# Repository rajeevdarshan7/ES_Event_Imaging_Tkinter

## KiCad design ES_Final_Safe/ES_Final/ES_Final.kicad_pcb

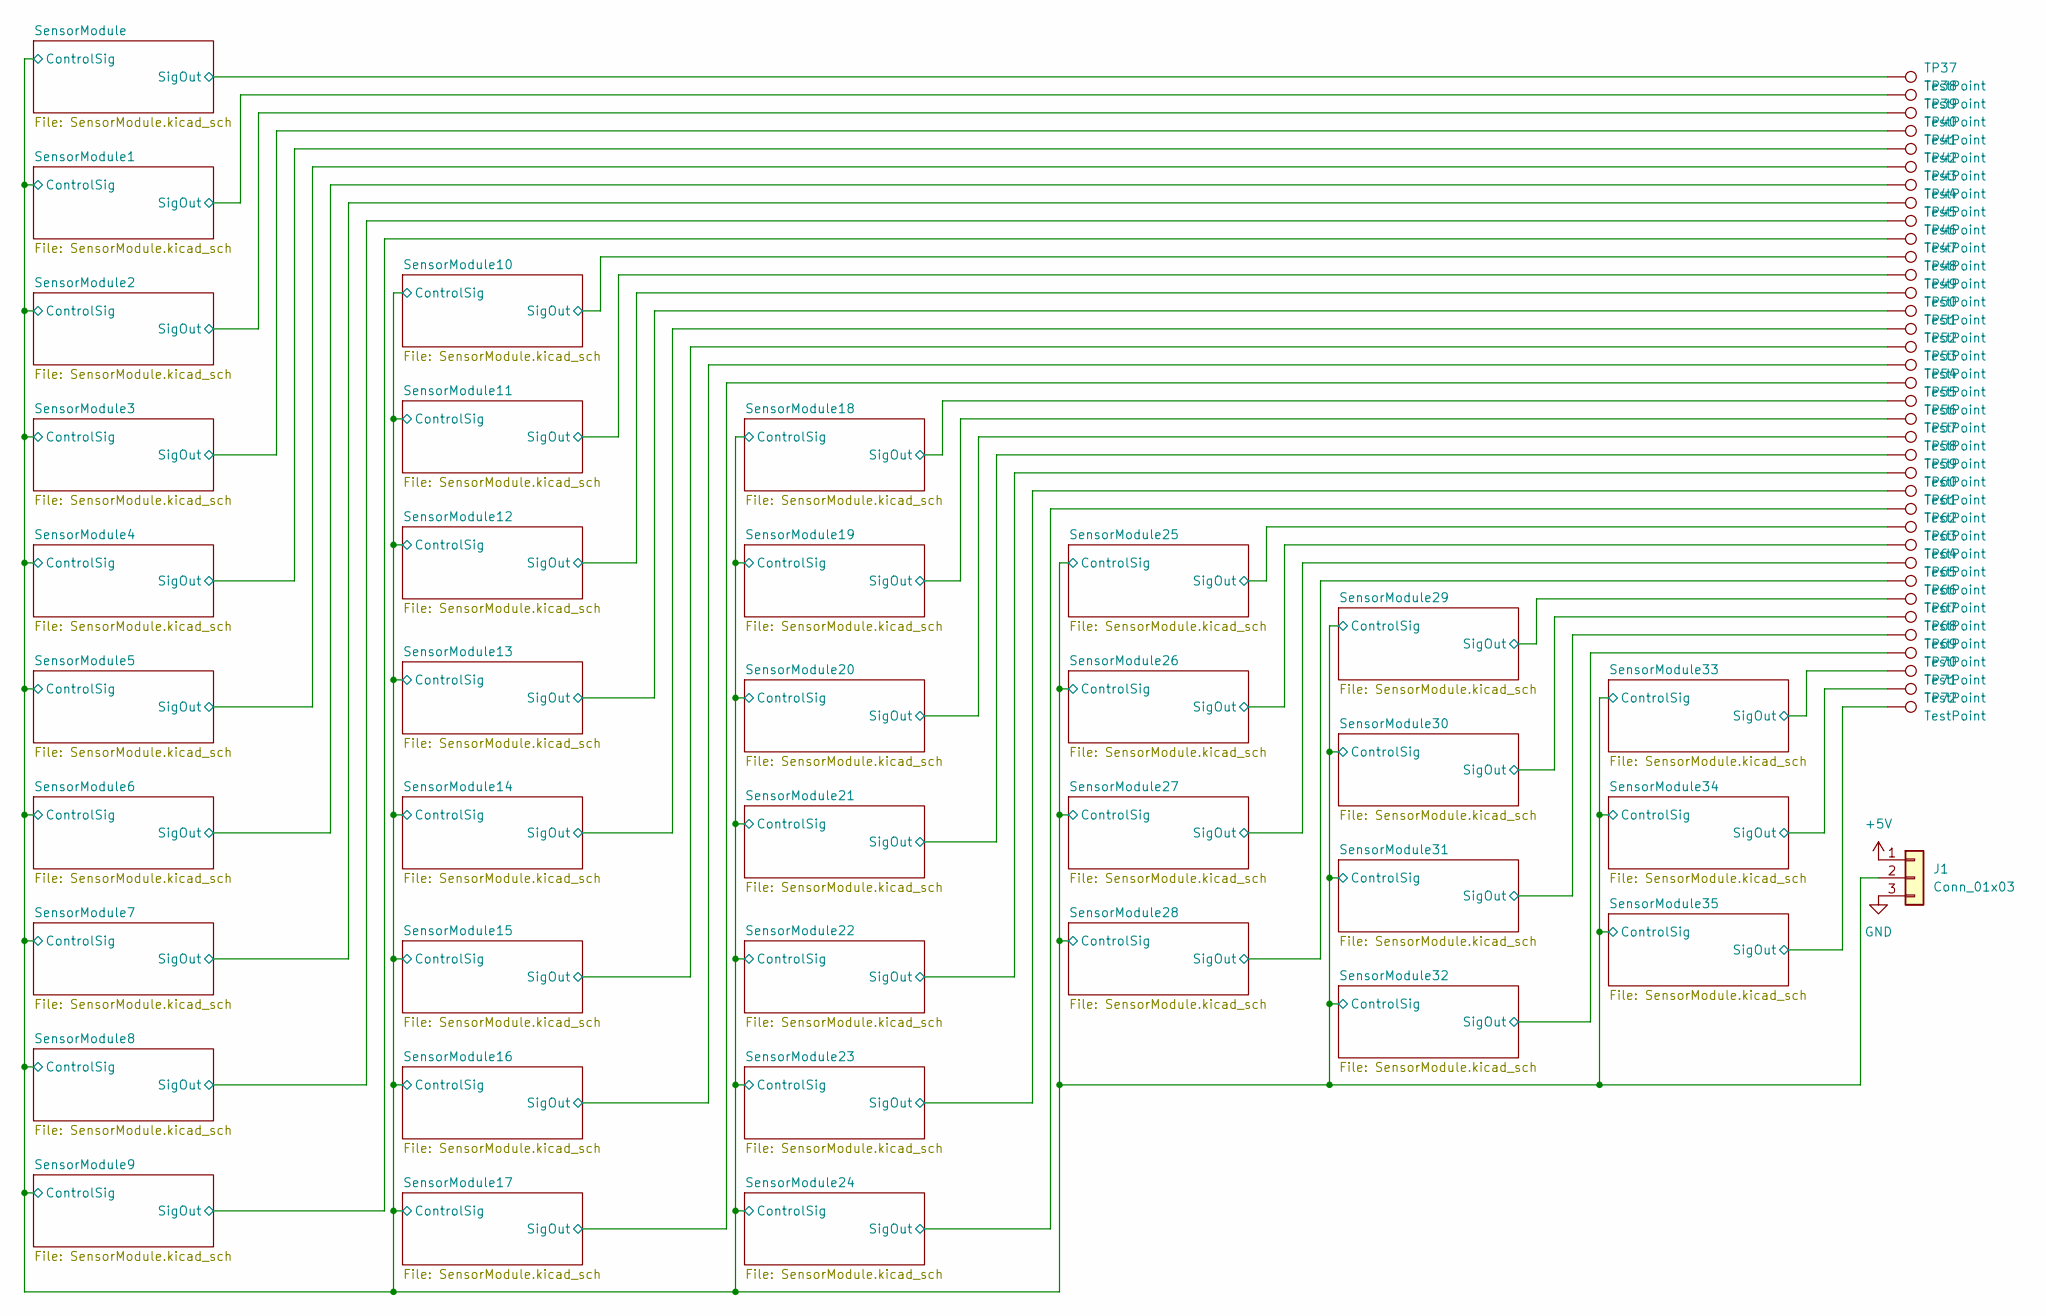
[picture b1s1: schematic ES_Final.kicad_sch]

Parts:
J1: Conn_01x03; JST_XH_B3B-XH-A_1x03_P2.50mm_Vertical
TP37, TP38, TP39, TP40, TP41, TP42, TP43, TP44, TP45, TP46, TP47, TP48, TP49, TP50, TP51, TP52, TP53, TP54, TP55, TP56, TP57, TP58, TP59, TP60, TP61, TP62, TP63, TP64, TP65, TP66, TP67, TP68, TP69, TP70, TP71, TP72: TestPoint; TestPoint_Pad_D1.0mm

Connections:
+5V: J1.1; also elsewhere on the board
/SensorModule1/SigOut: TP38.1; also elsewhere on the board
/SensorModule2/SigOut: TP39.1; also elsewhere on the board
/SensorModule3/SigOut: TP40.1; also elsewhere on the board
/SensorModule4/SigOut: TP41.1; also elsewhere on the board
/SensorModule5/SigOut: TP42.1; also elsewhere on the board
/SensorModule6/SigOut: TP43.1; also elsewhere on the board
/SensorModule7/SigOut: TP44.1; also elsewhere on the board
/SensorModule8/SigOut: TP45.1; also elsewhere on the board
/SensorModule9/SigOut: TP46.1; also elsewhere on the board
/SensorModule10/SigOut: TP47.1; also elsewhere on the board
/SensorModule11/SigOut: TP48.1; also elsewhere on the board
/SensorModule12/SigOut: TP49.1; also elsewhere on the board
/SensorModule13/SigOut: TP50.1; also elsewhere on the board
/SensorModule14/SigOut: TP51.1; also elsewhere on the board
/SensorModule15/SigOut: TP52.1; also elsewhere on the board
/SensorModule16/SigOut: TP53.1; also elsewhere on the board
/SensorModule17/SigOut: TP54.1; also elsewhere on the board
/SensorModule18/SigOut: TP55.1; also elsewhere on the board
/SensorModule19/SigOut: TP56.1; also elsewhere on the board
/SensorModule20/SigOut: TP57.1; also elsewhere on the board
/SensorModule21/SigOut: TP58.1; also elsewhere on the board
/SensorModule22/SigOut: TP59.1; also elsewhere on the board
/SensorModule23/SigOut: TP60.1; also elsewhere on the board
/SensorModule24/SigOut: TP61.1; also elsewhere on the board
/SensorModule25/SigOut: TP62.1; also elsewhere on the board
/SensorModule26/SigOut: TP63.1; also elsewhere on the board
/SensorModule27/SigOut: TP64.1; also elsewhere on the board
/SensorModule28/SigOut: TP65.1; also elsewhere on the board
/SensorModule29/SigOut: TP66.1; also elsewhere on the board
/SensorModule30/SigOut: TP67.1; also elsewhere on the board
/SensorModule31/SigOut: TP68.1; also elsewhere on the board
/SensorModule32/SigOut: TP69.1; also elsewhere on the board
/SensorModule33/SigOut: TP70.1; also elsewhere on the board
/SensorModule34/SigOut: TP71.1; also elsewhere on the board
/SensorModule35/SigOut: TP72.1; also elsewhere on the board
/SensorModule/ControlSig: J1.2; also elsewhere on the board
/SensorModule/SigOut: TP37.1; also elsewhere on the board
GND: J1.3; also elsewhere on the board

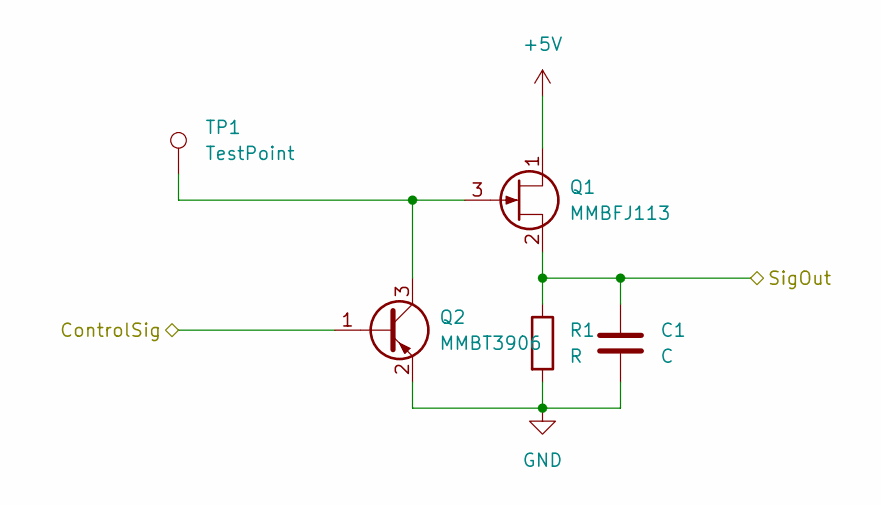
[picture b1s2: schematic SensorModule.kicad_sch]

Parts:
C1: C; C_0805_2012Metric_Pad1.18x1.45mm_HandSolder
Q1: MMBFJ113; SOT-23
Q2: MMBT3906; SOT-23
R1: R; R_0805_2012Metric_Pad1.20x1.40mm_HandSolder
TP1: TestPoint; TestPoint_Pad_1.0x1.0mm

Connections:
+5V: Q1.1 (D); also elsewhere on the board
/SensorModule/ControlSig: Q2.1 (B); also elsewhere on the board
/SensorModule/SigOut: C1.1, Q1.2 (S), R1.1; also elsewhere on the board
GND: C1.2, Q2.2 (E), R1.2; also elsewhere on the board
unnamed: Q1.3 (G), Q2.3 (C), TP1.1

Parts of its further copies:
C2, C3, C4, C5, C6, C7, C8, C9, C10, C11, C12, C13, C14, C15, C16, C17, C18, C19, C20, C21, C22, C23, C24, C25, C26, C27, C28, C29, C30, C31, C32, C33, C34, C35, C36: C; C_0805_2012Metric_Pad1.18x1.45mm_HandSolder
Q3, Q5, Q7, Q9, Q11, Q13, Q15, Q17, Q19, Q21, Q23, Q25, Q27, Q29, Q31, Q33, Q35, Q37, Q39, Q41, Q43, Q45, Q47, Q49, Q51, Q53, Q55, Q57, Q59, Q61, Q63, Q65, Q67, Q69, Q71: MMBT3906; SOT-23
Q4, Q6, Q8, Q10, Q12, Q14, Q16, Q18, Q20, Q22, Q24, Q26, Q28, Q30, Q32, Q34, Q36, Q38, Q40, Q42, Q44, Q46, Q48, Q50, Q52, Q54, Q56, Q58, Q60, Q62, Q64, Q66, Q68, Q70, Q72: MMBFJ113; SOT-23
R2, R3, R4, R5, R6, R7, R8, R9, R10, R11, R12, R13, R14, R15, R16, R17, R18, R19, R20, R21, R22, R23, R24, R25, R26, R27, R28, R29, R30, R31, R32, R33, R34, R35, R36: R; R_0805_2012Metric_Pad1.20x1.40mm_HandSolder
TP2, TP3, TP4, TP5, TP6, TP7, TP8, TP9, TP10, TP11, TP12, TP13, TP14, TP15, TP16, TP17, TP18, TP19, TP20, TP21, TP22, TP23, TP24, TP25, TP26, TP27, TP28, TP29, TP30, TP31, TP32, TP33, TP34, TP35, TP36: TestPoint; TestPoint_Pad_1.0x1.0mm

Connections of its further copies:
+5V: Q4.1 (D), Q6.1 (D), Q8.1 (D), Q10.1 (D), Q12.1 (D), Q14.1 (D), Q16.1 (D), Q18.1 (D), Q20.1 (D), Q22.1 (D), Q24.1 (D), Q26.1 (D), Q28.1 (D), Q30.1 (D), Q32.1 (D), Q34.1 (D), Q36.1 (D), Q38.1 (D), Q40.1 (D), Q42.1 (D), Q44.1 (D), Q46.1 (D), Q48.1 (D), Q50.1 (D), Q52.1 (D), Q54.1 (D), Q56.1 (D), Q58.1 (D), Q60.1 (D), Q62.1 (D), Q64.1 (D), Q66.1 (D), Q68.1 (D), Q70.1 (D), Q72.1 (D); also elsewhere on the board
/SensorModule1/SigOut: C2.1, Q4.2 (S), R2.1; also elsewhere on the board
/SensorModule2/SigOut: C3.1, Q6.2 (S), R3.1; also elsewhere on the board
/SensorModule3/SigOut: C4.1, Q8.2 (S), R4.1; also elsewhere on the board
/SensorModule4/SigOut: C5.1, Q10.2 (S), R5.1; also elsewhere on the board
/SensorModule5/SigOut: C6.1, Q12.2 (S), R6.1; also elsewhere on the board
/SensorModule6/SigOut: C7.1, Q14.2 (S), R7.1; also elsewhere on the board
/SensorModule7/SigOut: C8.1, Q16.2 (S), R8.1; also elsewhere on the board
/SensorModule8/SigOut: C9.1, Q18.2 (S), R9.1; also elsewhere on the board
/SensorModule9/SigOut: C10.1, Q20.2 (S), R10.1; also elsewhere on the board
/SensorModule10/SigOut: C11.1, Q22.2 (S), R11.1; also elsewhere on the board
/SensorModule11/SigOut: C12.1, Q24.2 (S), R12.1; also elsewhere on the board
/SensorModule12/SigOut: C13.1, Q26.2 (S), R13.1; also elsewhere on the board
/SensorModule13/SigOut: C14.1, Q28.2 (S), R14.1; also elsewhere on the board
/SensorModule14/SigOut: C15.1, Q30.2 (S), R15.1; also elsewhere on the board
/SensorModule15/SigOut: C16.1, Q32.2 (S), R16.1; also elsewhere on the board
/SensorModule16/SigOut: C17.1, Q34.2 (S), R17.1; also elsewhere on the board
/SensorModule17/SigOut: C18.1, Q36.2 (S), R18.1; also elsewhere on the board
/SensorModule18/SigOut: C19.1, Q38.2 (S), R19.1; also elsewhere on the board
/SensorModule19/SigOut: C20.1, Q40.2 (S), R20.1; also elsewhere on the board
/SensorModule20/SigOut: C21.1, Q42.2 (S), R21.1; also elsewhere on the board
/SensorModule21/SigOut: C22.1, Q44.2 (S), R22.1; also elsewhere on the board
/SensorModule22/SigOut: C23.1, Q46.2 (S), R23.1; also elsewhere on the board
/SensorModule23/SigOut: C24.1, Q48.2 (S), R24.1; also elsewhere on the board
/SensorModule24/SigOut: C25.1, Q50.2 (S), R25.1; also elsewhere on the board
/SensorModule25/SigOut: C26.1, Q52.2 (S), R26.1; also elsewhere on the board
/SensorModule26/SigOut: C27.1, Q54.2 (S), R27.1; also elsewhere on the board
/SensorModule27/SigOut: C28.1, Q56.2 (S), R28.1; also elsewhere on the board
/SensorModule28/SigOut: C29.1, Q58.2 (S), R29.1; also elsewhere on the board
/SensorModule29/SigOut: C30.1, Q60.2 (S), R30.1; also elsewhere on the board
/SensorModule30/SigOut: C31.1, Q62.2 (S), R31.1; also elsewhere on the board
/SensorModule31/SigOut: C32.1, Q64.2 (S), R32.1; also elsewhere on the board
/SensorModule32/SigOut: C33.1, Q66.2 (S), R33.1; also elsewhere on the board
/SensorModule33/SigOut: C34.1, Q68.2 (S), R34.1; also elsewhere on the board
/SensorModule34/SigOut: C35.1, Q70.2 (S), R35.1; also elsewhere on the board
/SensorModule35/SigOut: C36.1, Q72.2 (S), R36.1; also elsewhere on the board
/SensorModule/ControlSig: Q3.1 (B), Q5.1 (B), Q7.1 (B), Q9.1 (B), Q11.1 (B), Q13.1 (B), Q15.1 (B), Q17.1 (B), Q19.1 (B), Q21.1 (B), Q23.1 (B), Q25.1 (B), Q27.1 (B), Q29.1 (B), Q31.1 (B), Q33.1 (B), Q35.1 (B), Q37.1 (B), Q39.1 (B), Q41.1 (B), Q43.1 (B), Q45.1 (B), Q47.1 (B), Q49.1 (B), Q51.1 (B), Q53.1 (B), Q55.1 (B), Q57.1 (B), Q59.1 (B), Q61.1 (B), Q63.1 (B), Q65.1 (B), Q67.1 (B), Q69.1 (B), Q71.1 (B); also elsewhere on the board
GND: C2.2, C3.2, C4.2, C5.2, C6.2, C7.2, C8.2, C9.2, C10.2, C11.2, C12.2, C13.2, C14.2, C15.2, C16.2, C17.2, C18.2, C19.2, C20.2, C21.2, C22.2, C23.2, C24.2, C25.2, C26.2, C27.2, C28.2, C29.2, C30.2, C31.2, C32.2, C33.2, C34.2, C35.2, C36.2, Q3.2 (E), Q5.2 (E), Q7.2 (E), Q9.2 (E), Q11.2 (E), Q13.2 (E), Q15.2 (E), Q17.2 (E), Q19.2 (E), Q21.2 (E), Q23.2 (E), Q25.2 (E), Q27.2 (E), Q29.2 (E), Q31.2 (E), Q33.2 (E), Q35.2 (E), Q37.2 (E), Q39.2 (E), Q41.2 (E), Q43.2 (E), Q45.2 (E), Q47.2 (E), Q49.2 (E), Q51.2 (E), Q53.2 (E), Q55.2 (E), Q57.2 (E), Q59.2 (E), Q61.2 (E), Q63.2 (E), Q65.2 (E), Q67.2 (E), Q69.2 (E), Q71.2 (E), R2.2, R3.2, R4.2, R5.2, R6.2, R7.2, R8.2, R9.2, R10.2, R11.2, R12.2, R13.2, R14.2, R15.2, R16.2, R17.2, R18.2, R19.2, R20.2, R21.2, R22.2, R23.2, R24.2, R25.2, R26.2, R27.2, R28.2, R29.2, R30.2, R31.2, R32.2, R33.2, R34.2, R35.2, R36.2; also elsewhere on the board
unnamed: Q3.3 (C), Q4.3 (G), TP2.1
unnamed: Q5.3 (C), Q6.3 (G), TP3.1
unnamed: Q7.3 (C), Q8.3 (G), TP4.1
unnamed: Q9.3 (C), Q10.3 (G), TP5.1
unnamed: Q11.3 (C), Q12.3 (G), TP6.1
unnamed: Q13.3 (C), Q14.3 (G), TP7.1
unnamed: Q15.3 (C), Q16.3 (G), TP8.1
unnamed: Q17.3 (C), Q18.3 (G), TP9.1
unnamed: Q19.3 (C), Q20.3 (G), TP10.1
unnamed: Q21.3 (C), Q22.3 (G), TP11.1
unnamed: Q23.3 (C), Q24.3 (G), TP12.1
unnamed: Q25.3 (C), Q26.3 (G), TP13.1
unnamed: Q27.3 (C), Q28.3 (G), TP14.1
unnamed: Q29.3 (C), Q30.3 (G), TP15.1
unnamed: Q31.3 (C), Q32.3 (G), TP16.1
unnamed: Q33.3 (C), Q34.3 (G), TP17.1
unnamed: Q35.3 (C), Q36.3 (G), TP18.1
unnamed: Q37.3 (C), Q38.3 (G), TP19.1
unnamed: Q39.3 (C), Q40.3 (G), TP20.1
unnamed: Q41.3 (C), Q42.3 (G), TP21.1
unnamed: Q43.3 (C), Q44.3 (G), TP22.1
unnamed: Q45.3 (C), Q46.3 (G), TP23.1
unnamed: Q47.3 (C), Q48.3 (G), TP24.1
unnamed: Q49.3 (C), Q50.3 (G), TP25.1
unnamed: Q51.3 (C), Q52.3 (G), TP26.1
unnamed: Q53.3 (C), Q54.3 (G), TP27.1
unnamed: Q55.3 (C), Q56.3 (G), TP28.1
unnamed: Q57.3 (C), Q58.3 (G), TP29.1
unnamed: Q59.3 (C), Q60.3 (G), TP30.1
unnamed: Q61.3 (C), Q62.3 (G), TP31.1
unnamed: Q63.3 (C), Q64.3 (G), TP32.1
unnamed: Q65.3 (C), Q66.3 (G), TP33.1
unnamed: Q67.3 (C), Q68.3 (G), TP34.1
unnamed: Q69.3 (C), Q70.3 (G), TP35.1
unnamed: Q71.3 (C), Q72.3 (G), TP36.1

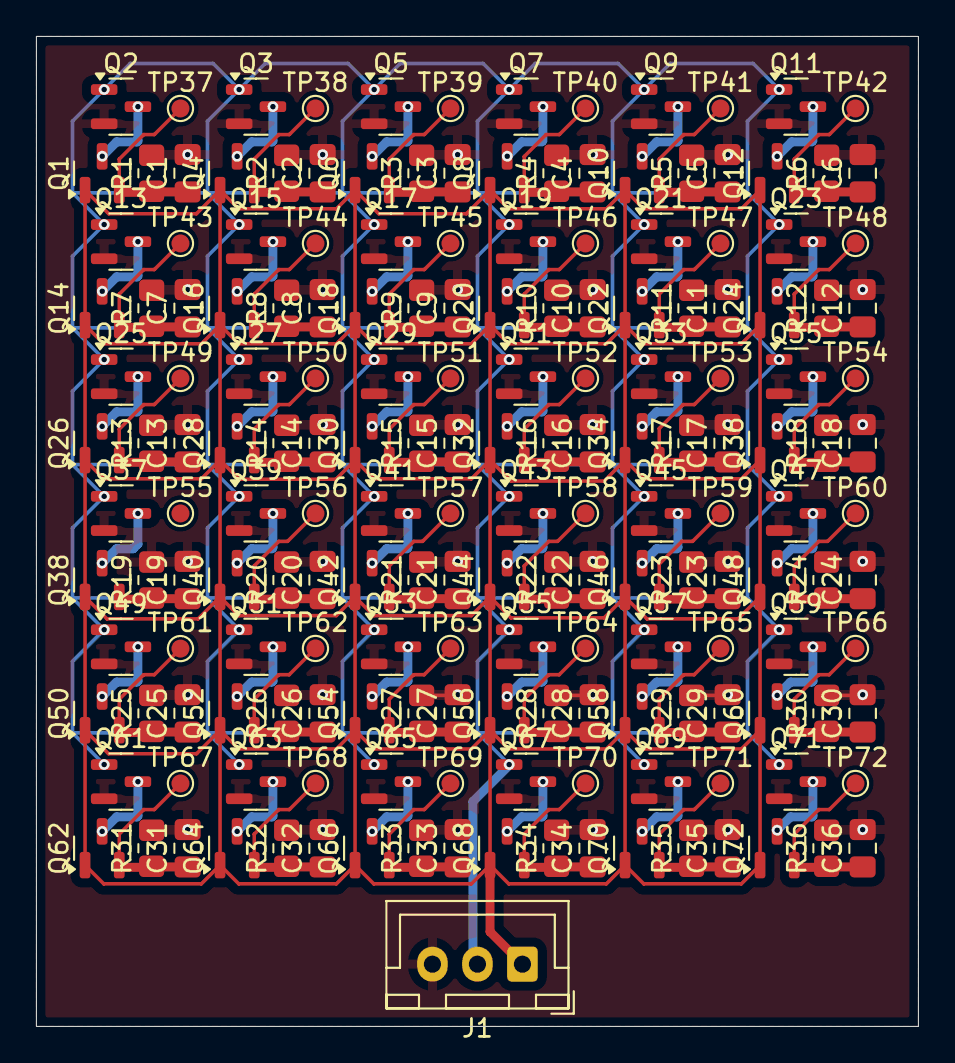
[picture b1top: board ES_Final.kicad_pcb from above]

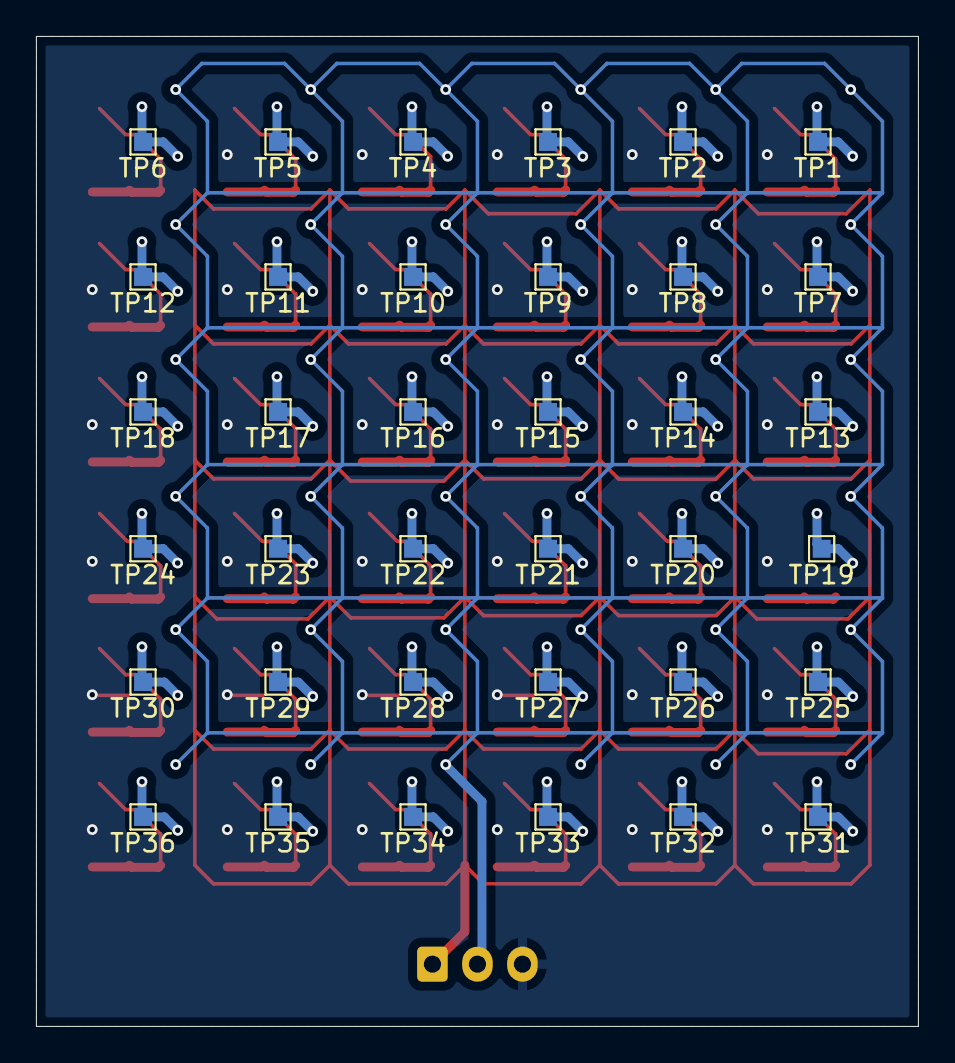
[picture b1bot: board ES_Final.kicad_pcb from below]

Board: 2 copper layers, 49.0 x 55.0 mm, 217 parts (36 on the bottom side), 75 nets.

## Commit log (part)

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2026-02-18 added requirements.txt
2026-02-18 added ES_Sensor_Modular for Arduino
2026-02-18 Added dropdown menu for different sensor arrays
2026-02-18 Change the name to ES Sensor
2026-02-18 Change to ES Sensor
2026-02-18 Added New Profiles + Dynamically Changing Array
2026-02-18 Changed theme from coffee to metal
2026-02-18 Add humidity GUI
2026-02-18 Changed Arduino Data Output Format
2026-02-18 change placement of humidity reading
2026-02-18 bugfix for Arduino Code
2026-02-18 added hunmidity label
2026-02-18 Added capture snapshot mode
2026-02-18 added increment step size
2026-02-18 fix all bugs for step size
2026-02-18 remove comments
2026-02-18 Bug fixes (Fixed buttons)
2026-02-18 Fixed Snapshot Mode + Arduino Serial Comms
2026-02-24 added theme directory
2026-02-24 added y-direction + bugfixes
2026-02-24 bugfixes
2026-02-24 interleaving y-direction fixed
2026-02-24 serial port greyed out fix
2026-04-18 updated for demo
2026-04-18 small bugfix
